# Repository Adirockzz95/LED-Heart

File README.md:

### LED-Heart
Repo contains:
Eagle LED heart PCB schematic files.

Arduino Code for LED heart project.

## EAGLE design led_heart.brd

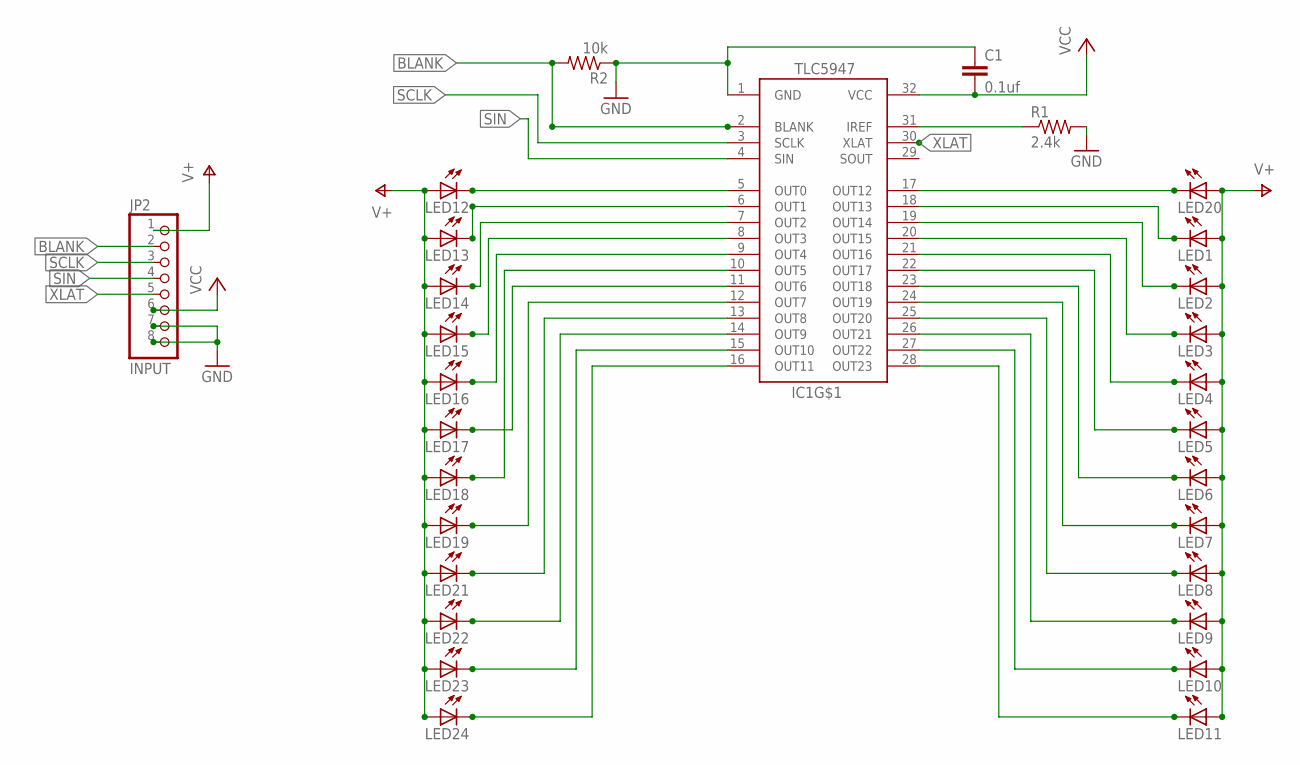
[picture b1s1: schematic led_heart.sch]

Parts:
C1: 0.1uf; C0805
IC1: TLC5947-DAP; HTSSOP32DAP
JP2: INPUT; 1X08-CLEANBIG
LED1, LED2, LED3, LED4, LED5, LED6, LED7, LED8, LED9, LED10, LED11, LED12, LED13, LED14, LED15, LED16, LED17, LED18, LED19, LED20, LED21, LED22, LED23, LED24: LEDCHIPLED_1206; CHIPLED_1206
R1: 2.4k; R0805
R2: 10k; R0805

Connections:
BLANK: IC1.2 (BLANK), JP2.2, R2.2
GND: C1.1, IC1.1 (GND), JP2.7, JP2.8, R1.2, R2.1
unnamed: IC1.19 (OUT14), LED2.C
unnamed: IC1.18 (OUT13), LED1.C
unnamed: IC1.17 (OUT12), LED20.C
unnamed: IC1.20 (OUT15), LED3.C
unnamed: IC1.21 (OUT16), LED4.C
unnamed: IC1.22 (OUT17), LED5.C
unnamed: IC1.23 (OUT18), LED6.C
unnamed: IC1.24 (OUT19), LED7.C
unnamed: IC1.25 (OUT20), LED8.C
unnamed: IC1.26 (OUT21), LED9.C
unnamed: IC1.27 (OUT22), LED10.C
unnamed: IC1.28 (OUT23), LED11.C
unnamed: IC1.5 (OUT0), LED12.C
unnamed: IC1.6 (OUT1), LED13.C
unnamed: IC1.7 (OUT2), LED14.C
unnamed: IC1.8 (OUT3), LED15.C
unnamed: IC1.9 (OUT4), LED16.C
unnamed: IC1.10 (OUT5), LED18.C
unnamed: IC1.11 (OUT6), LED17.C
unnamed: IC1.12 (OUT7), LED19.C
unnamed: IC1.13 (OUT8), LED21.C
unnamed: IC1.14 (OUT9), LED22.C
unnamed: IC1.15 (OUT10), LED23.C
unnamed: IC1.16 (OUT11), LED24.C
unnamed: IC1.31 (IREF), R1.1
SCLK: IC1.3 (SCLK), JP2.3
SIN: IC1.4 (SIN), JP2.4
V+: JP2.1, LED1.A, LED2.A, LED3.A, LED4.A, LED5.A, LED6.A, LED7.A, LED8.A, LED9.A, LED10.A, LED11.A, LED12.A, LED13.A, LED14.A, LED15.A, LED16.A, LED17.A, LED18.A, LED19.A, LED20.A, LED21.A, LED22.A, LED23.A, LED24.A
VCC: C1.2, IC1.32 (VCC), JP2.6
XLAT: IC1.30 (XLAT), JP2.5

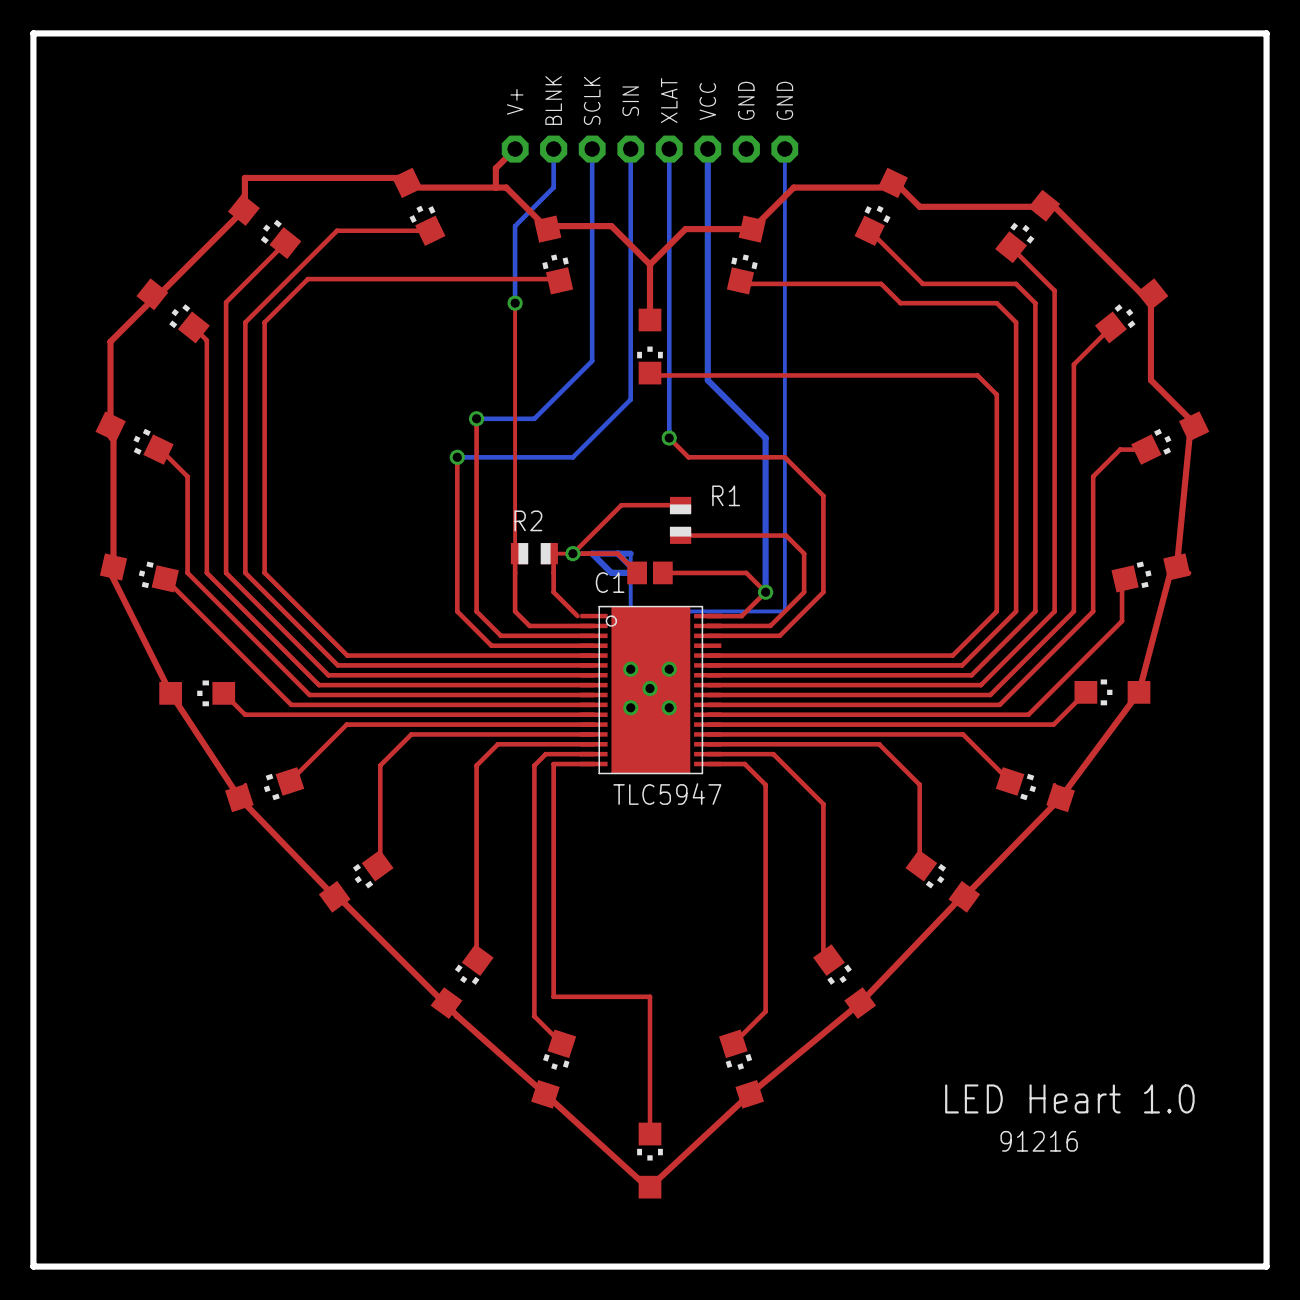
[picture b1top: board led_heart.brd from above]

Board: 2 copper layers, 81.3 x 81.3 mm, 29 parts (0 on the bottom side), 32 nets.

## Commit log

2017-01-25 Eagle schematic for TLC5947 Heart board
2017-01-25 Source code for LED heart project
